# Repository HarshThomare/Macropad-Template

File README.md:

# Macropad Template for Kicad

## Step 1: Install Kicad 6
https://www.kicad.org/download/

## Step 2: Download Template code

#### Method 1: Git

```
git clone https://github.com/HarshThomare/Macropad-Template.git
```

#### Method 2: Manual Download

Click Code > Download Zip

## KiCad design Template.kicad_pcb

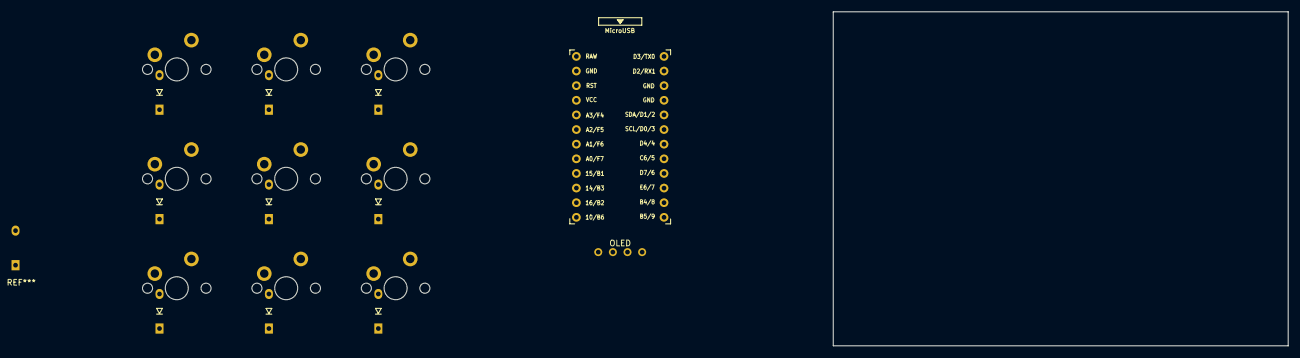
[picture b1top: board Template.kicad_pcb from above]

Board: 2 copper layers, 79.0 x 58.0 mm, 22 parts (1 on the bottom side), 20 nets, no tracks yet.

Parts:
D1, D2, D3, D4, D5, D6, D7, D8, D9: D_Small; D3_TH_nonHybrid
J1: OLED; OLED_v2
MX1, MX2, MX3, MX4, MX5, MX6, MX7, MX8, MX9: MX-NoLED; MXOnly-1U-NoLED
R1: 10k; R3_TH_nonHybrid
SW1: SW_Push; SW_SPST_TL3342
U1: ProMicro; ProMicro_v3

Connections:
+5V: J1.3, R1.1, U1.21 (VCC)
GND: J1.4, SW1.2, U1.3 (GND), U1.4 (GND), U1.23 (GND)
unnamed: D1.2 (A), MX1.1 (COL)
unnamed: D2.2 (A), MX2.1 (COL)
unnamed: D3.2 (A), MX3.1 (COL)
unnamed: D4.2 (A), MX4.1 (COL)
unnamed: D5.2 (A), MX5.1 (COL)
unnamed: D6.2 (A), MX6.1 (COL)
unnamed: D7.2 (A), MX7.1 (COL)
unnamed: D8.2 (A), MX8.1 (COL)
unnamed: D9.2 (A), MX9.1 (COL)
unnamed: R1.2, SW1.1, U1.22 (RST)
SCL: J1.2, U1.6 (SCL)
SDA: J1.1, U1.5 (SDA)
col0: MX1.2 (ROW), MX2.2 (ROW), MX3.2 (ROW), U1.16 (B1)
col1: MX4.2 (ROW), MX5.2 (ROW), MX6.2 (ROW), U1.17 (F7)
col2: MX7.2 (ROW), MX8.2 (ROW), MX9.2 (ROW), U1.18 (F6)
row0: D1.1 (K), D4.1 (K), D7.1 (K), U1.15 (B3)
row1: D2.1 (K), D5.1 (K), D8.1 (K), U1.14 (B2)
row2: D3.1 (K), D6.1 (K), D9.1 (K), U1.13 (B6)

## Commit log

2023-04-16 Starter Template
2023-04-16 Template files
2023-04-16 Create README.md
    Instructions
2023-04-17 Promicro symbol
2023-04-17 Added symbol to table
2023-04-21 Reset to blank
